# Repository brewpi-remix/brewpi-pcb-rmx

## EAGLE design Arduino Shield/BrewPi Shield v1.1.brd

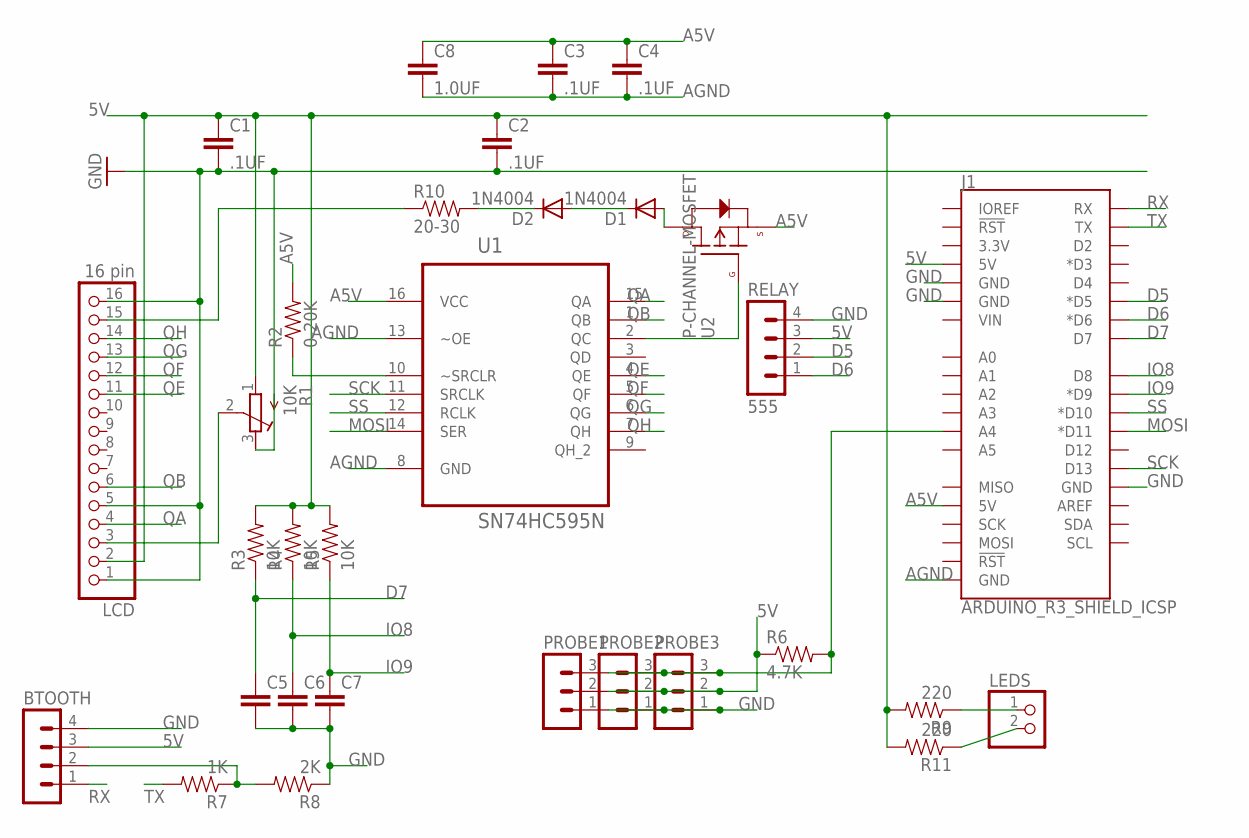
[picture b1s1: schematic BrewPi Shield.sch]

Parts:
BTOOTH: MA04-1
C1, C2, C3, C4: .1UF; CAP-PTH-SMALL-KIT
C5, C6, C7: CAPKIT; CAP-PTH-SMALL-KIT
C8: 1.0UF; CAP-PTH-SMALL-KIT
D1, D2: 1N4004; DO41-10
J1: ARDUINO_R3_SHIELD_ICSP; UNO_R3_SHIELD_ICSP
LCD: 16 pin; 1X16
LEDS: PINHD-1X2; 1X02
PROBE1, PROBE2, PROBE3: MA03-1
R1: 10K; RTRIM3296Y
R2: 0-20K; AXIAL-0.3
R3, R4, R5: 10K; AXIAL-0.3
R6: 4.7K; AXIAL-0.3
R7: 1K; AXIAL-0.3
R8: 2K; AXIAL-0.3
R9, R11: 220; AXIAL-0.3
R10: 20-30; AXIAL-0.5
RELAY: 555; MA04-1
U1: SN74HC595N; DIP254P762X508-16
U2: P-CHANNEL-MOSFET; SOT23-3

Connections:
5V: BTOOTH.3, C1.1, C2.1, J1.5V, LCD.2, PROBE1.2, PROBE2.2, PROBE3.2, R1.1 (A), R3.P$2 (2), R4.P$2 (2), R5.P$2 (2), R6.P$1 (1), R9.P$2 (2), R11.P$2 (2), RELAY.3
A5V: C3.1, C4.1, C8.1, J1.5V_ICSP (5V), R2.P$2 (2), U1.16 (VCC), U2.2 (S)
AGND: C3.2, C4.2, C8.2, J1.GND_ICSP (GND), U1.8 (GND), U1.13 (~OE)
D5: J1.D5 (*D5), RELAY.2
D6: J1.D6 (*D6), RELAY.1
D7: C5.1, J1.D7, R3.P$1 (1)
GND: BTOOTH.4, C1.2, C2.2, C5.2, C6.2, C7.2, J1.GND@0 (GND), J1.GND@1 (GND), J1.GND@2 (GND), LCD.1, LCD.5, LCD.16, PROBE1.1, PROBE2.1, PROBE3.1, R1.3 (E), R8.P$1 (1), RELAY.4
IO8: C6.1, J1.D8, R4.P$1 (1)
IO9: C7.1, J1.D9 (*D9), R5.P$1 (1)
MOSI: J1.D11 (*D11), U1.14 (SER)
unnamed: R2.P$1 (1), U1.10 (~SRCLR)
unnamed: U1.2 (QC), U2.1 (G)
unnamed: BTOOTH.2, R7.P$1 (1), R8.P$2 (2)
unnamed: J1.A4, PROBE1.3, PROBE2.3, PROBE3.3, R6.P$2 (2)
unnamed: D1.C, D2.A
unnamed: LCD.3, R1.2 (S)
unnamed: D2.C, R10.P$2 (2)
unnamed: LCD.15, R10.P$1 (1)
unnamed: D1.A, U2.3 (D)
unnamed: LEDS.1, R9.P$1 (1)
unnamed: LEDS.2, R11.P$1 (1)
QA: LCD.4, U1.15 (QA)
QB: LCD.6, U1.1 (QB)
QE: LCD.11, U1.4 (QE)
QF: LCD.12, U1.5 (QF)
QG: LCD.13, U1.6 (QG)
QH: LCD.14, U1.7 (QH)
RX: BTOOTH.1, J1.RX
SCK: J1.D13, U1.11 (SRCLK)
SS: J1.D10 (*D10), U1.12 (RCLK)
TX: J1.TX, R7.P$2 (2)

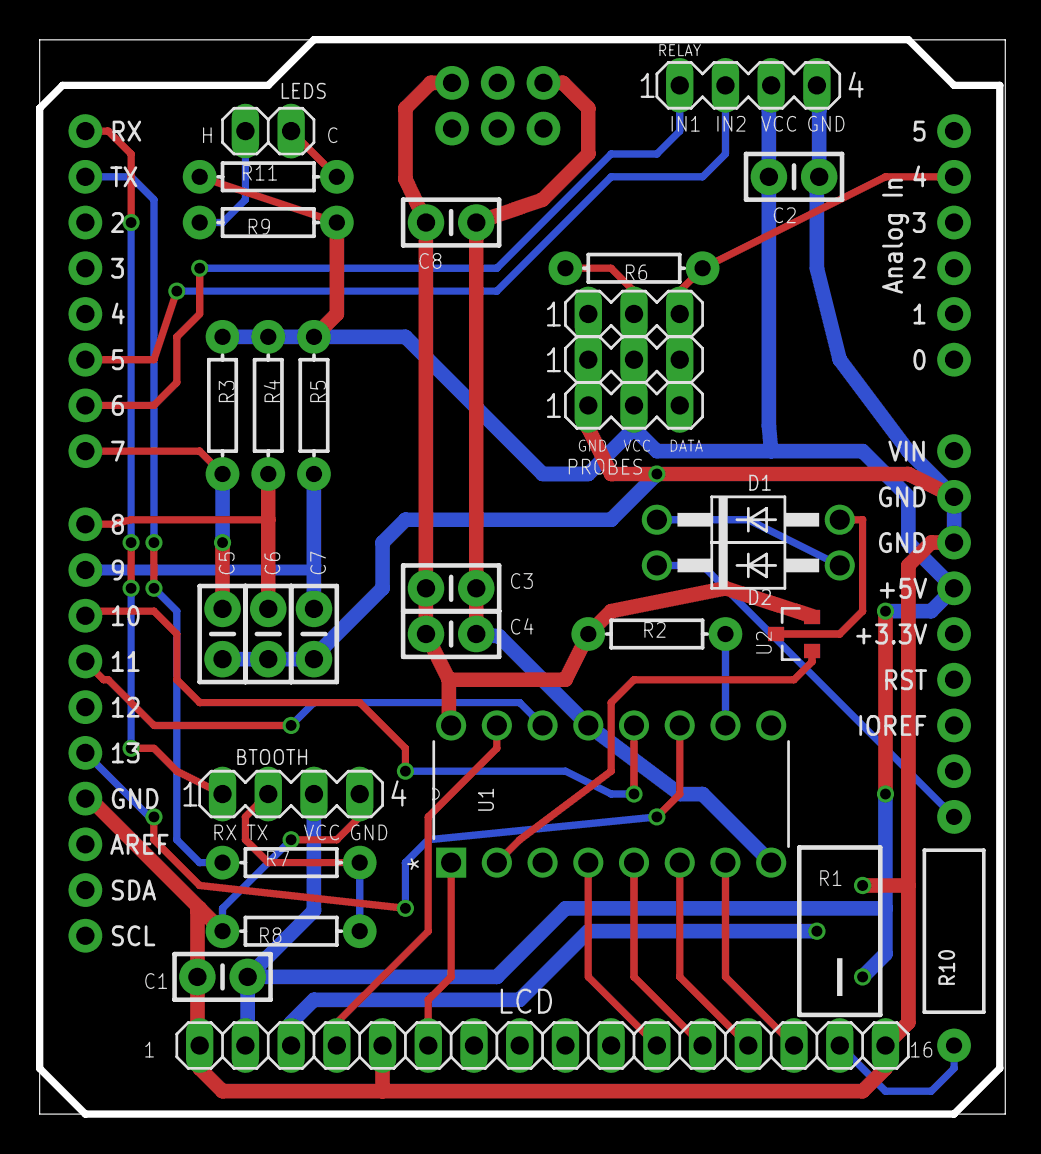
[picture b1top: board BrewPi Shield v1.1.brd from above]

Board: 2 copper layers, 53.6 x 59.7 mm, 31 parts (0 on the bottom side), 31 nets.

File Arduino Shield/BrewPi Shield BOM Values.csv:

"Qty";"Value";"Device";"Package";"Parts";"Description";"MF";"MPN";"OC_FARNELL";"OC_NEWARK";"PACKAGE";"SUPPLIER";
"3";"";"CAPKIT";"CAP-PTH-SMALL-KIT";"C5, C6, C7";"Capacitor";"";"";"";"";"";"";
"3";"";"MA03-1";"MA03-1";"PROBE1, PROBE2, PROBE3";"PIN HEADER";"";"";"unknown";"unknown";"";"";
"1";"";"MA04-1";"MA04-1";"BTOOTH";"PIN HEADER";"";"";"unknown";"unknown";"";"";
"1";"";"PINHD-1X2";"1X02";"LEDS";"PIN HEADER";"";"";"";"";"";"";
"4";".1UF";"CAPKIT";"CAP-PTH-SMALL-KIT";"C1, C2, C3, C4";"Capacitor";"";"";"";"";"";"";
"1";"0-20K";"RESISTORAXIAL-0.3";"AXIAL-0.3";"R2";"Resistor";"";"";"";"";"";"";
"1";"1.0UF";"CAPKIT";"CAP-PTH-SMALL-KIT";"C8";"Capacitor";"";"";"";"";"";"";
"1";"10K";"R-TRIMM3296Y";"RTRIM3296Y";"R1";"Trimm resistor";"";"";"";"";"";"";
"3";"10K";"RESISTORAXIAL-0.3";"AXIAL-0.3";"R3, R4, R5";"Resistor";"";"";"";"";"";"";
"1";"16 pin";"PINHD-1X16";"1X16";"LCD";"PIN HEADER";"";"";"";"";"";"";
"1";"1K";"RESISTORAXIAL-0.3";"AXIAL-0.3";"R7";"Resistor";"";"";"";"";"";"";
"2";"1N4004";"1N4004";"DO41-10";"D1, D2";"DIODE";"";"";"";"";"";"";
"1";"20-30";"RESISTORPTH-1/2W";"AXIAL-0.5";"R10";"Resistor";"";"";"";"";"";"";
"2";"220";"RESISTORAXIAL-0.3";"AXIAL-0.3";"R9, R11";"Resistor";"";"";"";"";"";"";
"1";"2K";"RESISTORAXIAL-0.3";"AXIAL-0.3";"R8";"Resistor";"";"";"";"";"";"";
"1";"4.7K";"RESISTORAXIAL-0.3";"AXIAL-0.3";"R6";"Resistor";"";"";"";"";"";"";
"1";"555";"MA04-1";"MA04-1";"RELAY";"PIN HEADER";"";"";"unknown";"unknown";"";"";
"1";"ARDUINO_R3_SHIELD_ICSP";"ARDUINO_R3_SHIELD_ICSP";"UNO_R3_SHIELD_ICSP";"J1";"Arduino R3 Shield Footprint w/ 6-pin (2x3) ICSP Header";"";"";"";"";"";"";
"1";"P-CHANNEL-MOSFET";"P-CHANNEL-MOSFET";"SOT23-3";"U2";"P-Channel MOSFET Mode Field Effect Transistor";"";"";"";"";"";"";
"1";"SN74HC595N";"SN74HC595N";"DIP254P762X508-16";"U1";"8-BIT SHIFT REGISTERS WITH 3-STATE OUTPUT REGISTERS";"";"SN74HC595N";"9591664";"60K6845";"PDIP-16";"Texas Instruments";

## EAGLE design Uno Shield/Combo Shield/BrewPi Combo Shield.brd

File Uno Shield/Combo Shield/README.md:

# 

# BrewPi Arduino Uno Shield v1.3.1a (I2C/Parallel LCD)

Arduino Uno shield for the [BrewPi Remix](https://www.brewpiremix.com) project. This is an new board design which incorporates an I2C LCD header in addition to the original parallel LCD header on the RevC.  The I2C display is supported in version 0.5.3 of BrewPi Legacy Remix Scripts, WWW and Tools, coupled with version 0.2.12 of the Arduino Firmware.

[Order from PCBs.io]():  (I removed this link because PCBs.io appear to have been overtaken by malware.  [OshPark](https://oshpark.com/) is a good choice for smaller quantities.)

- 2 Layer Board - 5.1164 sq in (2.1200in x 2.4134in) / 3300.9 sq/mm (53.85mm x 61.3mm)
- $19.39 per set of 4 ($3.79 per sq in)

## Supported Features:

  * Wireless to Serial Bridge (Bluetooth or ESP8266 module)
  * Door switch
  * Alarm
  * Heat/Cool Relay
  * Rotary Encoder w/Pushbutton
  * Heat/Cool LEDs
  * OneWire Selector A0/A4 (required for I2C)
  * Three OneWire connections
  * I2C LCD; or;
  * Parallel LCD
  * RJ45 connector includes support for:
    * OneWire
    * Door Switch
    * Heat/Cool Relay
  * All Arduino headers available

## Usage Notes:
Since this board is intended to support both the RevC as well as the I2C firmware, some configuration is required via jumper caps.

  - ONE_WIRE_SEL Jumper - If you do not select the proper configuration, you may not be able to configure the OneWire sensors, the display may fault, or both.
    - Jump between A4 and the center pin for RevC
    - Jump between A0 and the center pin for I2C
  - Backlight Timeout - If you do not have a rotary encoder you will not be able to wake the backlight if it times out.  You can configure the board to never turn off the backlight
    - RevC - The BACKLIGHT jumper has two settings:
      - Jump between ON and the center pin to have the backlight stay on
      - Jump between PB and the center pin to have the backlight time out
    - I2C - The backlight setting uses the rotary encoder header
      - If you have a rotary encoder, pushing the button during a controller reset will disable backlight timer
      - If you do not have a rotary encoder, adding a jumper on the ROT_ENC header between PSH and GND will disable backlight timer
  - Heat / Cool LEDs - You will use different connections for LEDs depending on the configuration of your actuators
    - Inverted (typical for relay board) - Connect the LED between VCC and the center pin.  A resistor is not needed as there is one on the board
    - Non-Inverted (typical for SSRs) - Connect the LED between the center pin and GND.  A resistor is not needed as there is one on the board

## BOM:

  * From Mouser (by using [this link](https://www.mouser.com/ProjectManager/ProjectDetail.aspx?AccessID=d74098d8b5) you can view all of these parts on Mouser and simply click the "Order Project" button):
    * 7 ea [0.1μF Ceramic Capacitor](https://www.mouser.com/ProductDetail/?qs=PmkNt%2FFLxQc4kNUCHU6a6Q%3D%3D) (C1-7)
    * 1 ea [1.0μF Ceramic Capacitor](https://www.mouser.com/ProductDetail/?qs=AQlKX63v8RtdX%2FUKFBhcig%3D%3D) (C8)
    * 1 ea [10kΩ Trimmer Resistor](https://www.mouser.com/ProductDetail/?qs=V3Em1enZyNPGF2%252BnCaKTKw%3D%3D) (R1)
    * 4 ea [10kΩ Axial Resistor 1/4W](https://www.mouser.com/ProductDetail/?qs=AtFvwFU%2F1FmCMXRebRRiVA%3D%3D) (R3-5, 12)
    * 1 ea [150Ω Axial Resistor 1/4W](https://www.mouser.com/ProductDetail/?qs=7jyBjEprRBipjkz1NPmruA%3D%3D) (R11)
    * 1 ea [1kΩ Axial Resistor 1/4W](https://www.mouser.com/ProductDetail/?qs=ddCg%252BR5cWn2sqOoxwN8P1g%3D%3D) (R8)
    * 1 ea [20kΩ Axial Resistor 1/4W](https://www.mouser.com/ProductDetail/KOA-Speer/MF1-4CC2002F?qs=sGAEpiMZZMu61qfTUdNhG%2Fir46E4ZSr2LQlauiwvExA%3D) (R2)
    * 2 ea [220Ω Axial Resistor 1/4W](https://www.mouser.com/ProductDetail/?qs=KVzGhl%2FcVV1aGF8Vc%2F%252BvDg%3D%3D) (R9, 10)
    * 1 ea [2kΩ Axial Resistor 1/4W](https://www.mouser.com/ProductDetail/?qs=iPPgFPFs9PM72iUDc08rBg%3D%3D) (R7)
    * 1 ea [4.7kΩ Axial Resistor 1/4W](https://www.mouser.com/ProductDetail/?qs=WbbykRgge7o4TK6QsdXS5A%3D%3D) (R6)
    * 1 ea [2N3906 PNP Transistor](https://www.mouser.com/ProductDetail/?qs=iN0KuJO79Kbn9o7a2lB4uA%3D%3D) (Q1)
    * 1 ea [SN74HC595N 8-Bit Shift Register](https://www.mouser.com/ProductDetail/?qs=IEl3ej0IqwBTHkYa8XPoMQ%3D%3D) (U1)
    * 1 ea [16-pin IC Socket](https://www.mouser.com/ProductDetail/?qs=5aG0NVq1C4zi9nx%252BGroISQ%3D%3D) (U1)
  * From Adafruit:
    * [Shield stacking headers for Arduino](https://www.adafruit.com/product/85)
    * [Break-away 0.1" 36-pin strip male header - Black - 10 pack](https://www.adafruit.com/product/392), more than enough for:
      * 2 ea 2-pin Header 2.54mm pitch (or 1 ea 4 pin)
      * 7 ea 3-pin Header 2.54mm pitch
      * 4 ea 4-pin Header 2.54mm pitch
      * 2 ea 6-pin Header 2.54mm pitch
  * 2 ea [Jumper Cap](https://www.amazon.com/ZYAMY-2-54mm-Standard-Circuit-Connection/dp/B077957RN7) (or you can use a female/female Dupont jumpers but caps are definitely better looking)
  * 1 ea [RJ45 Socket](https://www.aliexpress.com/item/High-Quality-20pcs-RJ45-8P8C-Computer-Internet-Network-PCB-Jack-Socket-Black/32736146888.html)

Other items you may want in order to complete your project:

  * LCD Display, either;
    * [20x4 LCD Parallel](https://www.amazon.com/SunFounder-Serial-Module-Arduino-Mega2560/dp/B071W8SW9R), or;
    * [20x4 LCD I2C](https://www.amazon.com/SunFounder-Serial-Module-Arduino-Mega2560/dp/B01GPUMP9C)
  * [5v 2-Channel Relay Module](https://www.amazon.com/gp/product/B00TMFVVG6)
  * [Rotary Encoder](https://www.mouser.com/ProductDetail/490-CZ11BR1E15FD120C)  - You want a magnetic encoder, no pull-ups, and 20 detents
  * [Knob for Rotary Encoder](https://www.mouser.com/ProductDetail/Eagle-Plastic-Devices/450-4763?qs=sGAEpiMZZMuiwDVLTMm01an1wsjHLopM%252Bn33k8wqz%252Bs%3D)
  * [Rotary Encoder Breakout Board](https://PCBs.io/share/zkPZ0)
  * At least two [DS18B20 Waterproof Temperature Sensors](https://www.amazon.com/gp/product/B01JKVRVNI)
  * Assorted [Dupont Jumper Wires](https://www.amazon.com/Multicolored-Breadboard-Dupont-Jumper-Wires/dp/B073X7P6N2) (male-male, male-female, female-female)

## Board Manufacture

You may order this board for manufacture directly from [pcbs.io](https://PCBs.io/share/zdeBw).

## 3D-Printed Case

See [this case](https://www.thingiverse.com/thing:3416312) from @gromitdj for a case you can print.

## Modifying These Files
If you would like to personalize these board designs, you may modify them with [Autodesk's EAGLE](https://www.autodesk.com/products/eagle/overview). EAGLE is a scriptable electronic design automation (EDA) application with schematic capture, printed circuit board (PCB) layout, auto-router and computer-aided manufacturing (CAM) features. EAGLE stands for Easily Applicable Graphical Layout Editor and is developed by CadSoft Computer GmbH. The company was acquired by Autodesk Inc. in 2016.  

The program supports Windows, Linux, and Mac OS X.  EAGLE is available in a [free version](https://www.autodesk.com/products/eagle/free-download), as well as a [subscription-based version with more features](https://www.autodesk.com/products/eagle/compare).

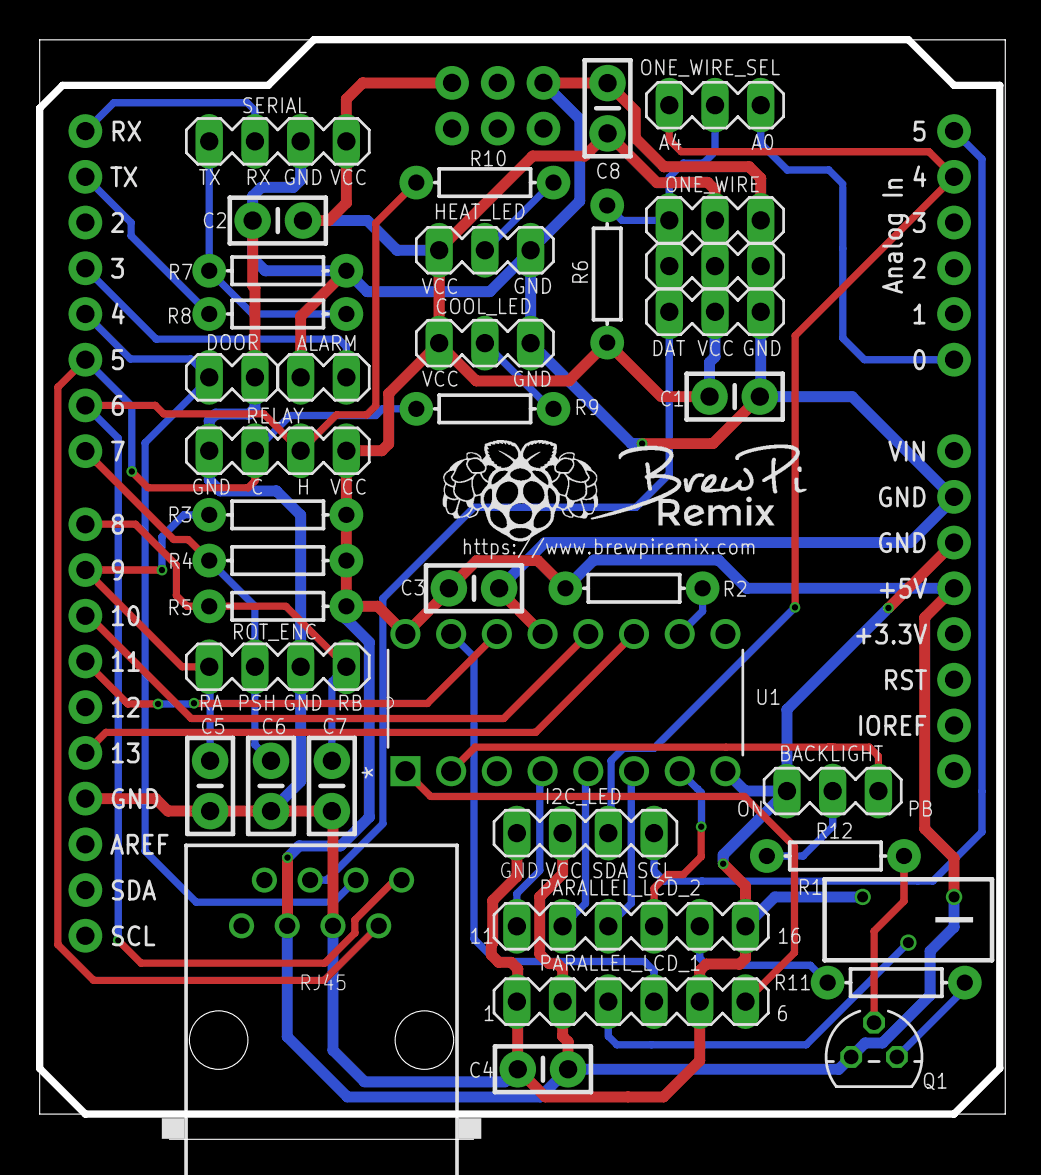
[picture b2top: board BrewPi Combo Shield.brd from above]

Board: 2 copper layers, 53.6 x 61.1 mm, 39 parts (0 on the bottom side), 34 nets.

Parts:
ALARM: 2 pin; HEADER02-1
BACKLIGHT: 3 pin; HEADER03-1
C1, C2, C3, C4, C5, C6, C7: 0.1μF; CAP-PTH-SMALL-KIT
C8: 1.0μF; CAP-PTH-SMALL-KIT
COOL_LED: 3 pin; HEADER03-1
DOOR: 2 pin; HEADER02-1
HEAT_LED: 3 pin; HEADER03-1
I2C_LED: 4 pin; HEADER04-1
J1: ARDUINO_R3_SHIELD_ICSP; UNO_R3_SHIELD_ICSP
ONE_WIRE_SEL: 3 pin; HEADER03-1
PARALLEL_LCD_1, PARALLEL_LCD_2: 6 pin; HEADER06-1
PROBE1, PROBE2, PROBE3: 3 pin; HEADER03-1
Q1: 2N3906; TO92
R1: 10kΩ; RTRIM3296Y
R2: 20kΩ; AXIAL-0.3
R3, R4, R5, R12: 10kΩ; AXIAL-0.3
R6: 4.7kΩ; AXIAL-0.3
R7: 2kΩ; AXIAL-0.3
R8: 1kΩ; AXIAL-0.3
R9, R10: 220Ω; AXIAL-0.3
R11: 150Ω; AXIAL-0.3
RELAY: 4 pin; HEADER04-1
RJ45: RJ45-8X; RJ45-NO-SHIELD
ROT_ENC: 4 pin; HEADER04-1
SERIAL: 4 pin; HEADER04-1
U1: SN74HC595N; DIP254P762X508-16

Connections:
1WIRE: ONE_WIRE_SEL.2, PROBE1.3, PROBE2.3, PROBE3.3, R6.P$2, RJ45.4
A0: J1.A0, ONE_WIRE_SEL.3
A4: I2C_LED.3, J1.A4, ONE_WIRE_SEL.1
A5: I2C_LED.4, J1.A5
ALARM: ALARM.1, J1.D3
COOL: J1.D5, R9.P$1, RELAY.2, RJ45.7
DOOR: DOOR.1, J1.D4, RJ45.6
GND: ALARM.2, BACKLIGHT.1, C1.2, C2.2, C3.2, C4.2, C5.2, C6.2, C7.2, C8.2, COOL_LED.3, DOOR.2, HEAT_LED.3, I2C_LED.1, J1.GND@0, J1.GND@1, J1.GND@2, J1.GND_ICSP, PARALLEL_LCD_1.1, PARALLEL_LCD_1.5, PARALLEL_LCD_2.6, PROBE1.1, PROBE2.1, PROBE3.1, R1.3, R7.P$1, RELAY.1, RJ45.5, ROT_ENC.3, SERIAL.3, U1.8, U1.13
HEAT: J1.D6, R10.P$2, RELAY.3, RJ45.8
MOSI: J1.D11, U1.14
unnamed: R2.P$1, U1.10
unnamed: BACKLIGHT.2, R12.P$1
unnamed: R7.P$2, R8.P$1, SERIAL.1
unnamed: COOL_LED.2, R9.P$2
unnamed: PARALLEL_LCD_2.5, R11.P$2
unnamed: PARALLEL_LCD_1.3, R1.2
unnamed: Q1.1, R11.P$1
unnamed: HEAT_LED.2, R10.P$1
unnamed: Q1.2, R12.P$2
PSHB: C6.1, J1.D7, R4.P$1, ROT_ENC.2
QA: PARALLEL_LCD_1.4, U1.15
QB: PARALLEL_LCD_1.6, U1.1
QC: BACKLIGHT.3, U1.2
QE: PARALLEL_LCD_2.1, U1.4
QF: PARALLEL_LCD_2.2, U1.5
QG: PARALLEL_LCD_2.3, U1.6
QH: PARALLEL_LCD_2.4, U1.7
ROTA: C5.1, J1.D9, R3.P$1, ROT_ENC.1
ROTB: C7.1, J1.D8, R5.P$1, ROT_ENC.4
RX: J1.RX, SERIAL.2
SCK: J1.D13, U1.11
SS: J1.D10, U1.12
TX: J1.TX, R8.P$2
VCC: C1.1, C2.1, C3.1, C4.1, C8.1, COOL_LED.1, HEAT_LED.1, I2C_LED.2, J1.5V, J1.5V_ICSP, PARALLEL_LCD_1.2, PROBE1.2, PROBE2.2, PROBE3.2, Q1.3, R1.1, R2.P$2, R3.P$2, R4.P$2, R5.P$2, R6.P$1, RELAY.4, RJ45.3, SERIAL.4, U1.16

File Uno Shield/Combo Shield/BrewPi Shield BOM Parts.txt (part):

Partlist exported from C:/Users/lee/OneDrive/Desktop/BrewPi/Git/brewpi-pcb-rmx/shield/BrewPi Shield.sch at 6/23/2019 4:01 PM

Part           Value                  Device                 Package            Description                                            MF MPN        OC_FARNELL OC_NEWARK PACKAGE SPICEMODEL SPICEPREFIXL SUPPLIER         
ALARM          2 pin                  HEADER02-1             HEADER02-1         PIN HEADER                                                                                                                                 
BACKLIGHT      3 pin                  HEADER03-1             HEADER03-1         PIN HEADER                                                           unknown    unknown                                                    
C1             0.1μF                  CAPKIT                 CAP-PTH-SMALL-KIT  Capacitor                                                                                                                                  
C2             0.1μF                  CAPKIT                 CAP-PTH-SMALL-KIT  Capacitor                                                                                                                                  
C3             0.1μF                  CAPKIT                 CAP-PTH-SMALL-KIT  Capacitor                                                                                                                                  
C4             0.1μF                  CAPKIT                 CAP-PTH-SMALL-KIT  Capacitor                                                                                                                                  
C5             0.1μF                  CAPKIT                 CAP-PTH-SMALL-KIT  Capacitor                                                                                                                                  
C6             0.1μF                  CAPKIT                 CAP-PTH-SMALL-KIT  Capacitor                                                                                                                                  
C7             0.1μF                  CAPKIT                 CAP-PTH-SMALL-KIT  Capacitor                                                                                                                                  
C8             1.0μF                  CAPKIT                 CAP-PTH-SMALL-KIT  Capacitor                                                                                                                                  
COOL_LED       3 pin                  HEADER03-1             HEADER03-1         PIN HEADER                                                           unknown    unknown                                                    
DOOR           2 pin                  HEADER02-1             HEADER02-1         PIN HEADER                                                                                                                                 
HEAT_LED       3 pin                  HEADER03-1             HEADER03-1         PIN HEADER                                                           unknown    unknown                                                    
I2C_LED        4 pin                  HEADER04-1             HEADER04-1         PIN HEADER                                                           unknown    unknown                                                    
J1             ARDUINO_R3_SHIELD_ICSP ARDUINO_R3_SHIELD_ICSP UNO_R3_SHIELD_ICSP Arduino R3 Shield Footprint w/ 6-pin (2x3) ICSP Header                                                                                     
ONE_WIRE_SEL   3 pin                  HEADER03-1             HEADER03-1         PIN HEADER                                                           unknown    unknown                                                    
PARALLEL_LCD_1 6 pin                  HEADER06-1             HEADER06-1         PIN HEADER                                                           unknown    unknown                                                    
PARALLEL_LCD_2 6 pin                  HEADER06-1             HEADER06-1         PIN HEADER                                                           unknown    unknown                                                    
PROBE1         3 pin                  HEADER03-1             HEADER03-1         PIN HEADER                                                           unknown    unknown                                                    
PROBE2         3 pin                  HEADER03-1             HEADER03-1         PIN HEADER                                                           unknown    unknown                                                    
PROBE3         3 pin                  HEADER03-1             HEADER03-1         PIN HEADER                                                           unknown    unknown                                                    
Q1             2N3906                 2N3906                 TO92               PNP Transistor                                                                                                                             
R1             10kΩ                   R-TRIMM3296Y           RTRIM3296Y         Trimm resistor                                                                                    X          POT                           
R2             20kΩ                   RESISTORAXIAL-0.3      AXIAL-0.3          Resistor                                                                                                                                   
R3             10kΩ                   RESISTORAXIAL-0.3      AXIAL-0.3          Resistor                                                                                                                                   
R4             10kΩ                   RESISTORAXIAL-0.3      AXIAL-0.3          Resistor                                                                                                                                   
R5             10kΩ                   RESISTORAXIAL-0.3      AXIAL-0.3          Resistor                                                                                                                                   
R6             4.7kΩ                  RESISTORAXIAL-0.3      AXIAL-0.3          Resistor                                                                                                                                   
R7             2kΩ                    RESISTORAXIAL-0.3      AXIAL-0.3          Resistor                                                                                                                                   
R8             1kΩ                    RESISTORAXIAL-0.3      AXIAL-0.3          Resistor                                                                                                                                   
R9             220Ω                   RESISTORAXIAL-0.3      AXIAL-0.3          Resistor                                                                                                                                   
R10            220Ω                   RESISTORAXIAL-0.3      AXIAL-0.3          Resistor                                                                                                                                   
R11            150Ω                   RESISTORAXIAL-0.3      AXIAL-0.3          Resistor                                                                                                                                   
R12            10kΩ                   RESISTORAXIAL-0.3      AXIAL-0.3          Resistor                                                                                                                                   
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
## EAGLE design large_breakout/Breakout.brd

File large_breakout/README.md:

# 
# BrewPi Breakout v1.3.1a

Breakout Board for the [BrewPi Legacy Remix](https://www.brewpiremix.com) project.

This optional breakout board is intended to be connected to the Arduino Shield v1.3.1a via a straight-through RJ45 terminated cable (i.e. an Ethernet cable.)  It allows the Arduino to be located remotely from the fermentation chamber.

## Supported Features:

  * Door switch
  * Heat/Cool
    * Dupont pins
    * Screw terminal
  * Heat/Cool LEDs
  * Temp Sensors
    * Three Dupont pin sets
    * Three screw terminals

## Usage Notes:
Since this board is intended to support multiple configurations, some customization during assembly is required.

  - Heat / Cool LEDs - You will use different connections for LEDs depending on the configuration of your actuators.  Connections are provided for two LEDs each for heat and cool, however you will only use one based on your setup
    - Inverted (typical for relay board) - Connect the LED between VCC and the center pin.  A resistor is not needed as there is one on the board
    - Non-Inverted (typical for SSRs) - Connect the LED between the center pin and GND.  A resistor is not needed as there is one on the board

## BOM:

  * 1 ea [Red 3mm LED](https://www.mouser.com/ProductDetail/638-MV5064.MP4B)
  * 1 ea [Blue 3mm LED](https://www.mouser.com/ProductDetail/941-C503BBCNCV0Z0461)
  * 2 ea [220Ω 1/4W Axial Resistors](https://www.mouser.com/ProductDetail/660-MF1-4DCT52R2200F)
  * 1 ea 4-Pin header
  * 1 ea 2-Pin header
  * 3 ea 3-Pin headers
  * 1 ea RJ45 terminal
  * 3 ea 3-Position screw terminal
  * 1 ea 4-Position screw terminal
  * 1 ea 2-Position screw terminal

## Board Manufacture
You may order this board for manufacture directly from [OshPark](https://oshpark.com/shared_projects/SfXfFd61).

## Modifying These Files
If you would like to personalize these board designs, you may modify them with [Autodesk's EAGLE](https://www.autodesk.com/products/eagle/overview). EAGLE is a scriptable electronic design automation (EDA) application with schematic capture, printed circuit board (PCB) layout, auto-router and computer-aided manufacturing (CAM) features. EAGLE stands for Easily Applicable Graphical Layout Editor and is developed by CadSoft Computer GmbH. The company was acquired by Autodesk Inc. in 2016.  

The program supports Windows, Linux, and Mac OS X.  EAGLE is available in a [free version](https://www.autodesk.com/products/eagle/free-download), as well as a [subscription-based version with more features](https://www.autodesk.com/products/eagle/compare).

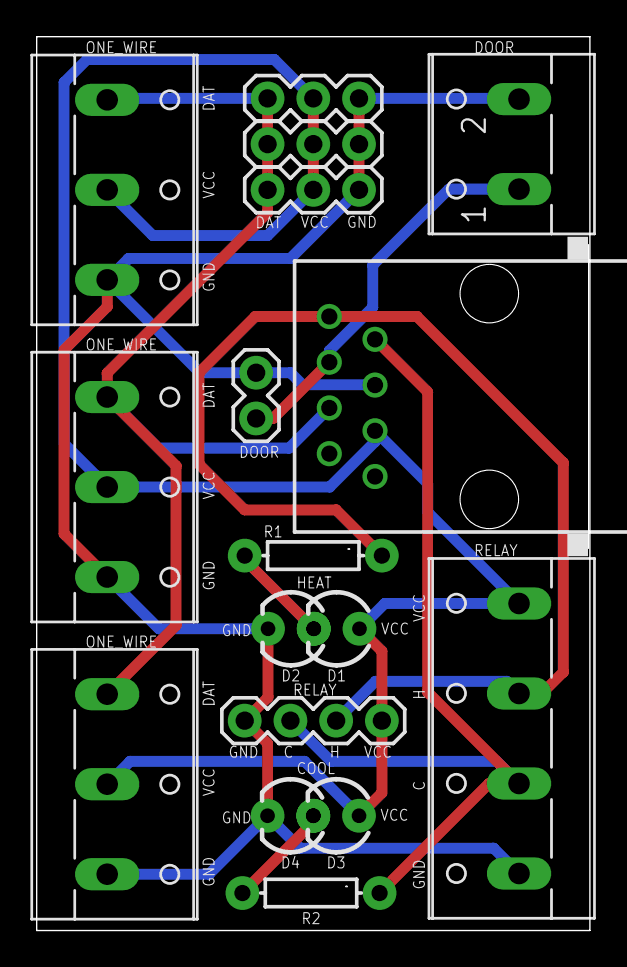
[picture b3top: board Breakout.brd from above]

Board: 2 copper layers, 30.7 x 49.7 mm, 17 parts (0 on the bottom side), 8 nets.

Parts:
D1: HINV; LED_3MM
D2: HNON; LED_3MM
D3: CINV; LED_3MM
D4: CNON; LED_3MM
DOOR: 2-PIN; 1X02
ONE_WIRE1, ONE_WIRE2, ONE_WIRE3: 3-PIN; 1X03
R1, R2: 220Ω; AXIAL-0.3
RELAY: 4-PIN; 1X04
RELAY_TERM: 4TERM; W237-4
X1: RJ45-8X; RJ45-NO-SHIELD
X2: 4TERM; W237-102
X3, X4, X5: 3TERM; W237-103

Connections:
COOL: R2.P$1, RELAY.2, RELAY_TERM.2, X1.7
DATA: ONE_WIRE1.3, ONE_WIRE2.3, ONE_WIRE3.3, X1.4, X3.1, X4.1, X5.1
DOOR: DOOR.2, X1.6, X2.1
GND: D2.K, D4.K, DOOR.1, ONE_WIRE1.1, ONE_WIRE2.1, ONE_WIRE3.1, RELAY.1, RELAY_TERM.1, X1.5, X2.2, X3.3, X4.3, X5.3
HEAT: R1.P$1, RELAY.3, RELAY_TERM.3, X1.8
unnamed: D1.K, D2.A, R1.P$2
unnamed: D3.K, D4.A, R2.P$2
VCC: D1.A, D3.A, ONE_WIRE1.2, ONE_WIRE2.2, ONE_WIRE3.2, RELAY.4, RELAY_TERM.4, X1.3, X3.2, X4.2, X5.2

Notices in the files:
parts and their libraries:
SparkFun-Capacitors: Licensing: Creative Commons ShareAlike 4.0 International - https://creativecommons.org/licenses/by-sa/4.0
